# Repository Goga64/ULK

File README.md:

# ULK

Low profile split keyboard with Corne 42 Layout and Cherry ULP switches. Made to be used on top of a laptop keyboard to provide the ultimate split experience on the go. 

## Contents
   - [Description](#Description)
   - [Gallery](#Gallery)
   - [BOM](#BOM)
   - [Firmware](#Firmware)
   - [Inspirations](#Inspirations)

# Description

## Switches
### Sound  
I have recorded some [samples](https://github.com/Goga64/ULK/tree/e7978e2b8ab778f136db2aed6a6b6116afc4dded/Sound). For all of them the keyboard was on a mousepad.

I prefer the sound of the ULP Click, although it is still not as nice as the full size switches.

### Feel
The Cherry ULP feel quite satifying to type on, however they are a bit heavy coming in at 65g. The PG1316s though I'm not as impressed by, I got the 35g version which is very light, it makes the typing feel effortless, it doesn't really feel like anything. With it I also struggle with typos while writing as extra letters will just appear out of nowhere. It is definetry something I need to get used to before I can give a better oppinion. I will probably want to try the 60g version of them in the future and if they made a 50g version I would build another keeb with them immediately.  

## Firmware
The non-solar versions use standard Conre ZMK firmware.

The solar version however is diodeless, thus it is direct wired. So you should use my a modified verion of the MC Technology's zmk-config [GitHub link](https://github.com/Goga64/zmk-config-ULK)

The firmware was one of the biggest roadblock in getting the whole thing working. As it has 21 keys per side it uses all of the GPIO avaliable on a ProMicro including three marked purple here:

As they are not included in the original pinout on the main ZMK branch I needed fork and change the [pinout](https://github.com/Goga64/zmk/blob/v0.3-branch/app/boards/arm/nice_nano/arduino_pro_micro_pins.dtsi) to include them. 

I have also not wired up both sides as a mirror of each other on the PCB which has lead to a weird [keymap_transform](https://github.com/Goga64/zmk-config-ULK/blob/7f940e578cdd5d7742a9fed1b120f3a784b748a8/boards/shields/ulk_sl/ulk_sl.dtsi).

## Things to do: 
   - Add a 3x5 option.
   - Update BOM for sl version
   - Solar writeup

## Gallery
More images can be found in the [Gallery folder](https://github.com/Goga64/ULK/tree/953767bf9aa2bdcd04b6005427a60ab565788cff/Gallery).
They were taken on a Cannon EOS5D mkii (2008) and an EF 24-70mm F/2.8 USM lens.

I had a lot of fun focus stacking them for the best sharpness.

# BOM 

## Main Components (for the non solar version)

| Name             | Specification                                                                 | Notes                                             |
|------------------|-------------------------------------------------------------------------------|---------------------------------------------------|
| Switches         | Cherry ULP or Kailh PG1316S                                                   | You can find more about the ULP at [Cherry_MX_ULP](https://github.com/pashutk/Cherry_MX_ULP)                                                |
| Keycaps          | 1U Kailh PG1316S Keycaps                                                      | —                                                 |
| Diodes           | 1N4148W in SOD-123 package                                                    | —                                                 |
| Microcontroller  | SuperMini NRF52840                                                            | Compatible with nice!nano V2 and alternatives ([GitHub link](https://github.com/joric/nrfmicro/wiki/Alternatives)) |
| Power switch     | 7Pin Mini Slide Switch                                                        | —                                                 |
| Reset button     | 3x6x4.3mm push button                                                         | Will change to an smd one after testing samples   |
| Battery          | ~100mAh 401525 LiPo or smaller                                                | Prototype photos show 750mAh HiV battery due to shipping delays |

## Optional Components

| Name        | Specification                                       | Notes                                             |
|-------------|---------------------------------------------------|---------------------------------------------------|
| Non-slip    | 1 mm Silicone Rubber Strip, Self Adhesive           | Increases overall thickness to 6.8mm              |
| Kapton tape | Polyimide insulating tape                           | To cover through-hole components on bottom of PCB |

<!---
## BOM
Switches - Cherry ULP or Khali PG1316S
Keycaps - 1U Kailh PG1316S Keycaps 
Diodes - 1N4148W in SOD-123 package
Microcontroller - SuperMini NRF52840 - compatable with nice!nano V2 and it's alternatives https://github.com/joric/nrfmicro/wiki/Alternatives
Power switch - 7Pin Mini Slide Switch
Reset button -  3x6x4.3mm push button - Will probably be changed, when I get a sample of buttons.
Battery - ~100mAh 401525 Lipo or smaller - On the pictures a 750 mAh HiV battery is used due to battery shipping taking a long time and I had those lying around.

Optional
Non-slip - 1 mm Silicone Rubber Strip Self Adhesive (thinkness increases to 6.8mm).
Capton tape - to cover the through hole components on the bottom side of the pcb.
-->

## Inspirations
- [foostan/crkbd](https://github.com/foostan/crkbd)
- [mctechnology17/zmk-config](https://github.com/mctechnology17/zmk-config)
- [pashutk/Cherry_MX_ULP](https://github.com/pashutk/Cherry_MX_ULP)
- [zmk-config-mikefive](https://github.com/mikeholscher/zmk-config-mikefive)
- [ZMK](https://zmk.dev/)

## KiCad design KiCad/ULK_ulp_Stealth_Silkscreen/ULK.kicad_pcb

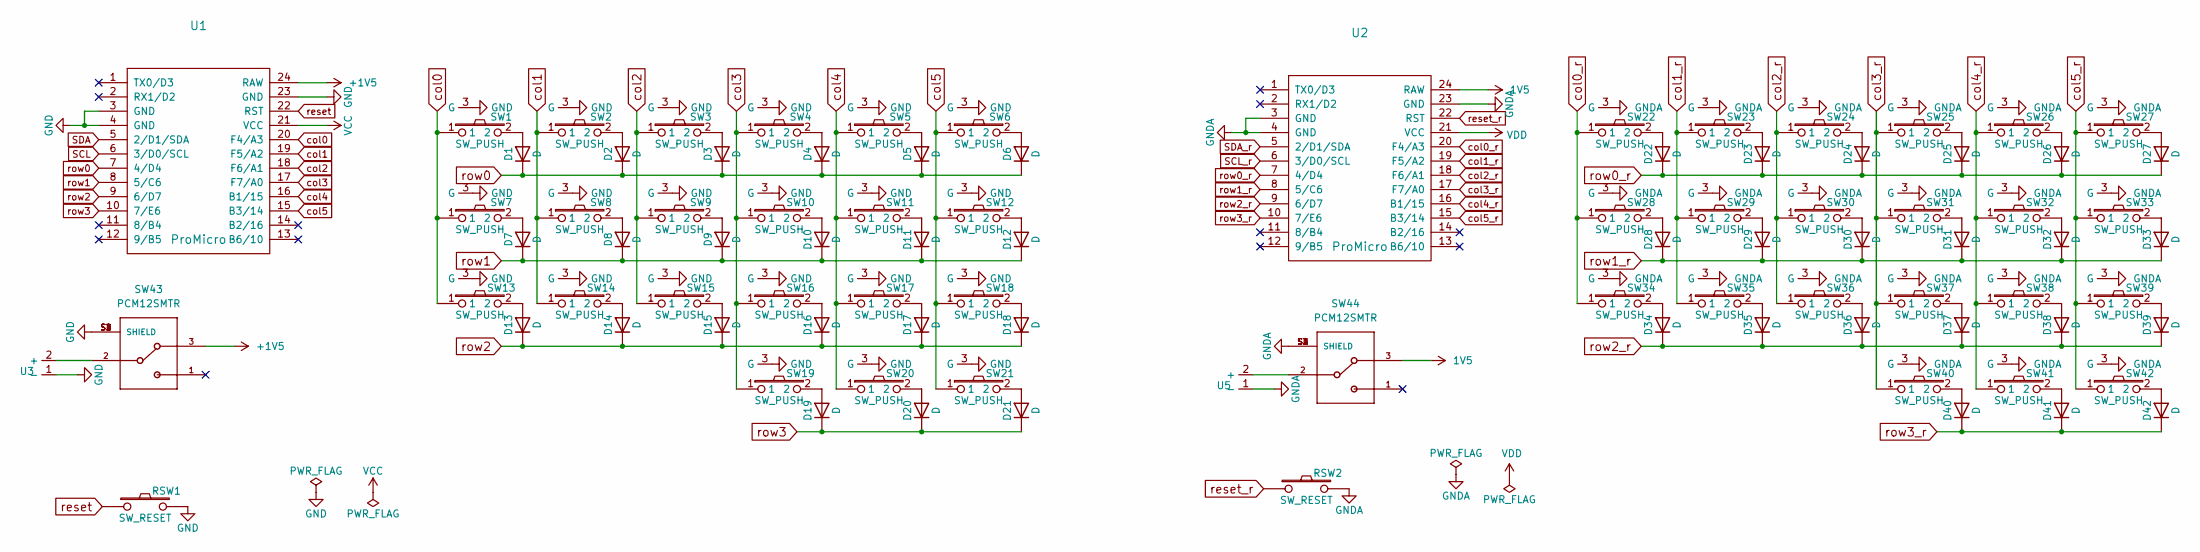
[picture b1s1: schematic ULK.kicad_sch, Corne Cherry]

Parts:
D1, D2, D3, D4, D5, D6, D7, D8, D9, D10, D11, D12, D13, D14, D15, D16, D17, D18, D19, D20, D21, D22, D23, D24, D25, D26, D27, D28, D29, D30, D31, D32, D33, D34, D35, D36, D37, D38, D39, D40, D41, D42: D; D3_SMD_v2
RSW1, RSW2: SW_RESET; ResetSW_1side
SW1, SW2, SW3, SW4, SW5, SW6, SW7, SW8, SW9, SW10, SW11, SW12, SW13, SW14, SW15, SW16, SW17, SW18, SW19, SW20, SW21, SW22, SW23, SW24, SW25, SW26, SW27, SW28, SW29, SW30, SW31, SW32, SW33, SW34, SW35, SW36, SW37, SW38, SW39, SW40, SW41, SW42: SW_PUSH; Cherry_ULP_SMD
SW43, SW44: PCM12SMTR; SW_PCM12SMTR
U1, U2: ProMicro; ProMicro_v3
U3, U5: PinHeader_1x02_P2.54mm_Vertical

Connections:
1V5: SW44.3, U2.24 (RAW)
+1V5: SW43.3, U1.24 (RAW)
GND: RSW1.2, SW1.3 (G), SW2.3 (G), SW3.3 (G), SW4.3 (G), SW5.3 (G), SW6.3 (G), SW7.3 (G), SW8.3 (G), SW9.3 (G), SW10.3 (G), SW11.3 (G), SW12.3 (G), SW13.3 (G), SW14.3 (G), SW15.3 (G), SW16.3 (G), SW17.3 (G), SW18.3 (G), SW19.3 (G), SW20.3 (G), SW21.3 (G), SW43.S1 (SHIELD), SW43.S2 (SHIELD), SW43.S3 (SHIELD), SW43.S4 (SHIELD), U1.3 (GND), U1.4 (GND), U1.23 (GND), U3.1 (-)
GNDA: RSW2.2, SW22.3 (G), SW23.3 (G), SW24.3 (G), SW25.3 (G), SW26.3 (G), SW27.3 (G), SW28.3 (G), SW29.3 (G), SW30.3 (G), SW31.3 (G), SW32.3 (G), SW33.3 (G), SW34.3 (G), SW35.3 (G), SW36.3 (G), SW37.3 (G), SW38.3 (G), SW39.3 (G), SW40.3 (G), SW41.3 (G), SW42.3 (G), SW44.S1 (SHIELD), SW44.S2 (SHIELD), SW44.S3 (SHIELD), SW44.S4 (SHIELD), U2.3 (GND), U2.4 (GND), U2.23 (GND), U5.1 (-)
unnamed: D1.2 (A), SW1.2
unnamed: D2.2 (A), SW2.2
unnamed: D3.2 (A), SW3.2
unnamed: D4.2 (A), SW4.2
unnamed: D5.2 (A), SW5.2
unnamed: D6.2 (A), SW6.2
unnamed: D7.2 (A), SW7.2
unnamed: D8.2 (A), SW8.2
unnamed: D9.2 (A), SW9.2
unnamed: D10.2 (A), SW10.2
unnamed: D11.2 (A), SW11.2
unnamed: D12.2 (A), SW12.2
unnamed: D13.2 (A), SW13.2
unnamed: D14.2 (A), SW14.2
unnamed: D15.2 (A), SW15.2
unnamed: D16.2 (A), SW16.2
unnamed: D17.2 (A), SW17.2
unnamed: D18.2 (A), SW18.2
unnamed: D19.2 (A), SW19.2
unnamed: D20.2 (A), SW20.2
unnamed: D21.2 (A), SW21.2
unnamed: D22.2 (A), SW22.2
unnamed: D23.2 (A), SW23.2
unnamed: D24.2 (A), SW24.2
unnamed: D25.2 (A), SW25.2
unnamed: D26.2 (A), SW26.2
unnamed: D27.2 (A), SW27.2
unnamed: D28.2 (A), SW28.2
unnamed: D29.2 (A), SW29.2
unnamed: D30.2 (A), SW30.2
unnamed: D31.2 (A), SW31.2
unnamed: D32.2 (A), SW32.2
unnamed: D33.2 (A), SW33.2
unnamed: D34.2 (A), SW34.2
unnamed: D35.2 (A), SW35.2
unnamed: D36.2 (A), SW36.2
unnamed: D37.2 (A), SW37.2
unnamed: D38.2 (A), SW38.2
unnamed: D39.2 (A), SW39.2
unnamed: D40.2 (A), SW40.2
unnamed: D41.2 (A), SW41.2
unnamed: D42.2 (A), SW42.2
unnamed: SW43.2, U3.2 (+)
unnamed: SW44.2, U5.2 (+)
SCL: U1.6 (3/D0/SCL)
SCL_r: U2.6 (3/D0/SCL)
SDA: U1.5 (2/D1/SDA)
SDA_r: U2.5 (2/D1/SDA)
VCC: U1.21 (VCC)
VDD: U2.21 (VCC)
col0: SW1.1, SW7.1, SW13.1, U1.20 (F4/A3)
col0_r: SW22.1, SW28.1, SW34.1, U2.20 (F4/A3)
col1: SW2.1, SW8.1, SW14.1, U1.19 (F5/A2)
col1_r: SW23.1, SW29.1, SW35.1, U2.19 (F5/A2)
col2: SW3.1, SW9.1, SW15.1, U1.18 (F6/A1)
col2_r: SW24.1, SW30.1, SW36.1, U2.18 (F6/A1)
col3: SW4.1, SW10.1, SW16.1, SW19.1, U1.17 (F7/A0)
col3_r: SW25.1, SW31.1, SW37.1, SW40.1, U2.17 (F7/A0)
col4: SW5.1, SW11.1, SW17.1, SW20.1, U1.16 (B1/15)
col4_r: SW26.1, SW32.1, SW38.1, SW41.1, U2.16 (B1/15)
col5: SW6.1, SW12.1, SW18.1, SW21.1, U1.15 (B3/14)
col5_r: SW27.1, SW33.1, SW39.1, SW42.1, U2.15 (B3/14)
reset: RSW1.1, U1.22 (RST)
reset_r: RSW2.1, U2.22 (RST)
row0: D1.1 (K), D2.1 (K), D3.1 (K), D4.1 (K), D5.1 (K), D6.1 (K), U1.7 (4/D4)
row0_r: D22.1 (K), D23.1 (K), D24.1 (K), D25.1 (K), D26.1 (K), D27.1 (K), U2.7 (4/D4)
row1: D7.1 (K), D8.1 (K), D9.1 (K), D10.1 (K), D11.1 (K), D12.1 (K), U1.8 (5/C6)
row1_r: D28.1 (K), D29.1 (K), D30.1 (K), D31.1 (K), D32.1 (K), D33.1 (K), U2.8 (5/C6)
row2: D13.1 (K), D14.1 (K), D15.1 (K), D16.1 (K), D17.1 (K), D18.1 (K), U1.9 (6/D7)
row2_r: D34.1 (K), D35.1 (K), D36.1 (K), D37.1 (K), D38.1 (K), D39.1 (K), U2.9 (6/D7)
row3: D19.1 (K), D20.1 (K), D21.1 (K), U1.10 (7/E6)
row3_r: D40.1 (K), D41.1 (K), D42.1 (K), U2.10 (7/E6)

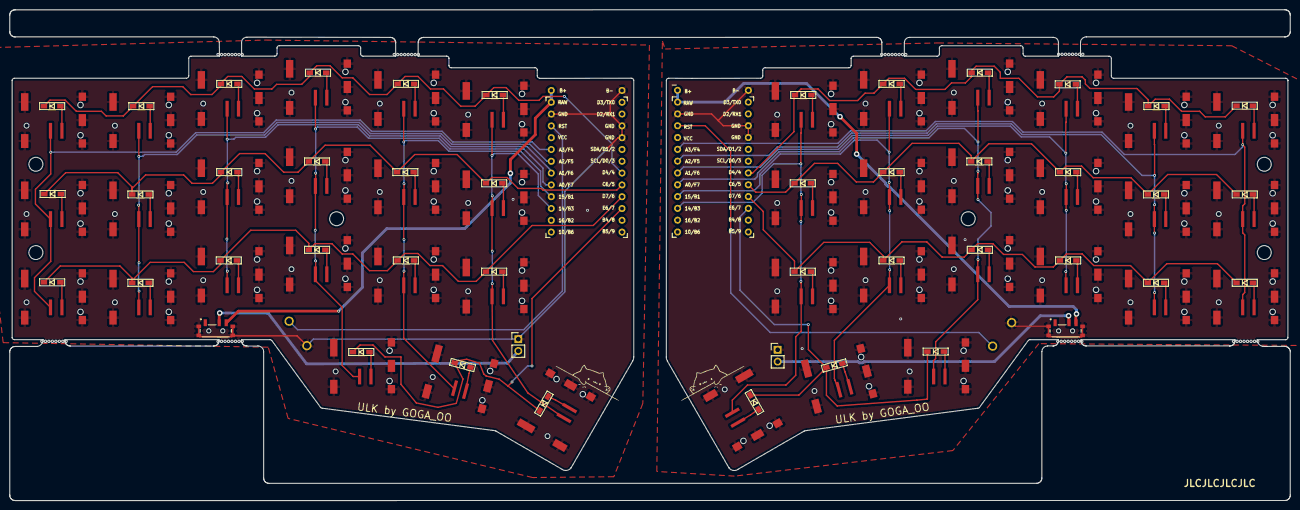
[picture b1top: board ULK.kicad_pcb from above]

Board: 2 copper layers, 275.5 x 105.6 mm, 100 parts (0 on the bottom side), 70 nets.

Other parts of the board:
mouse-bite-2mm-slot, mouse-bite-2mm-slot#2, mouse-bite-2mm-slot#3, mouse-bite-2mm-slot#4, mouse-bite-2mm-slot#5, mouse-bite-2mm-slot#6, mouse-bite-2mm-slot#7, mouse-bite-2mm-slot#8: VAL**; mouse-bite-2mm-slot

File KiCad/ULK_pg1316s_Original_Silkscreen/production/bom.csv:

Designator,Footprint,Quantity,Value,LCSC Part #
"D1, D10, D11, D12, D13, D14, D15, D16, D17, D18, D19, D2, D20, D21, D22, D23, D24, D25, D26, D27, D28, D29, D3, D30, D31, D32, D33, D34, D35, D36, D37, D38, D39, D4, D40, D41, D42, D5, D6, D7, D8, D9",D3_SMD_v2,42,D,
"MOUSE-BITE-2MM-SLOT_8, MOUSE-BITE-2MM-SLOT_7, MOUSE-BITE-2MM-SLOT_6, MOUSE-BITE-2MM-SLOT_5, MOUSE-BITE-2MM-SLOT_4, MOUSE-BITE-2MM-SLOT_3, MOUSE-BITE-2MM-SLOT_2, MOUSE-BITE-2MM-SLOT",mouse-bite-2mm-slot,8,VAL**,
"RSW1, RSW2",ResetSW_1side,2,SW_PUS,
"SW1, SW10, SW11, SW12, SW13, SW14, SW15, SW16, SW17, SW18, SW19, SW2, SW20, SW21, SW22, SW23, SW24, SW25, SW26, SW27, SW28, SW29, SW3, SW30, SW31, SW32, SW33, SW34, SW35, SW36, SW37, SW38, SW39, SW4, SW40, SW41, SW42, SW5, SW6, SW7, SW8, SW9",CPG1316S01D02_kailhspecsheet_mikefive,42,SW_PUSH,
"SW43, SW44",SW_PCM12SMTR,2,PCM12SMTR,
"U1, U2",ProMicro_v3,2,ProMicro,
"U3, U5",PinHeader_1x02_P2.54mm_Vertical,2,~,

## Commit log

2025-06-16 first
2025-06-16 Added all contents from Cherry_MX_ULP
2025-06-16 Readme
2025-06-16 Revert "Readme"
    This reverts commit 451b137922adf389a886915dadfc9d76a75c6557.
2025-06-16 Revert "Added all contents from Cherry_MX_ULP"
    This reverts commit 58726e41956fe9afe2040e367dcca494d9e4f393.
2025-06-16 Revert "Add files via upload"
    This reverts commit 6f8d5c44d196924c14e02aa596787fb68a29ea2a.
2025-06-16 Added all files from Cherry_MX_ULP
2025-09-12 push
2025-09-16 renders
2025-09-17 gound planes
2025-09-17 ulp update ground plane
2025-09-17 ulp gound plane
2025-09-17 Added PG1316S pcb
2025-09-27 Create LICENSE
2025-09-27 Update issue templates
2025-09-27 Update LICENSE
2025-10-11 grammar
2025-10-12 pg1316s 1.0.3
2026-04-16 Solar + restructuring
2026-04-16 Photos
2026-04-16 cover photo
2026-04-16 sounds
2026-04-16 more sounds
2026-04-16 Update the README for the Solar version releaser
